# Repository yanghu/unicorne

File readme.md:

# Unicorne - A single-piece 40% ortho keyboard inspired by Corne and more.

This is the keyboard design files for my own use, inspired by
[crkbd](https://github.com/foostan/crkbd),
[Kyria](https://blog.splitkb.com/blog/introducing-the-kyria) and
[Ferris](https://github.com/pierrechevalier83/ferris), as well as
[Reviung41](https://github.com/gtips/reviung) and others.

The name means "uni(single-piece)corne".

## Summary of board features

* USB-C connector
* Audio buzzer
* Rotary encoder x 2 (optional)
* Underglow RGB LEDs x8
* SMT32 MCU (STM32F411)
* OLED display
* Column stagger similar to Kyria.
* Corne-style thumb cluster with extra inner key: I feel Kyria's thumb cluster 
is too much and the outer column is hard to reach for me. 
* Thumb cluster shifted 0.25u to the middle.

## Links

* [PCB repo](unicorne-mx/unicorne).
* [PCB ibom
](https://yanghu.github.io/unicorne/artifacts/ibom/unicorn-ibom.html)
* [Fabrication files and firmware](https://github.com/yanghu/unicorne/releases/tag/v1.0)
* [QMK firmware repo](https://github.com/yanghu/qmk_firmware/tree/unicorne/keyboards/yanghu/unicorne).
* [Build guide](https://github.com/yanghu/unicorne/wiki/Build-guide)

## Why I designed this board

I like the simplicity of Corne, however, the more aggresive column stagger
on Kyria suits my hand better. I also removed the use of pro micro boards, and
followed Ferris 2.0 with an ARM chip directly on the board.

The initial reason I wanted to design this board is to eliminate the ugly
"add-on" board of promicro. Ferris is nice but I needed a 3x6 with full thumb
clusters as well: portability is not an issue for me.

I initially thought about building a split keyboard, however, after used crkbd
for a while, I missed the simplicity of a one-piece board: it's always symmetric
and has smaller footprint.

I do use a Planck, but *ortho* is not really a good idea on traditional keyboard
layout: the hands are so close and it's awkward to keep hands "vertical": the
wrist really is painful, especially after used to more ergonomic splits.

Reviung-like keyboards really gave me the inspiration. The angle ensures arms
and hands are in line, while you can still use the ortho layout.

Other features are nice and in different designs. I like the buzzer on Planck
that tells you when the keyboard is alive. The small OLED really is useful to
display status information for a programmable board. The encoder can be pretty
versatile.

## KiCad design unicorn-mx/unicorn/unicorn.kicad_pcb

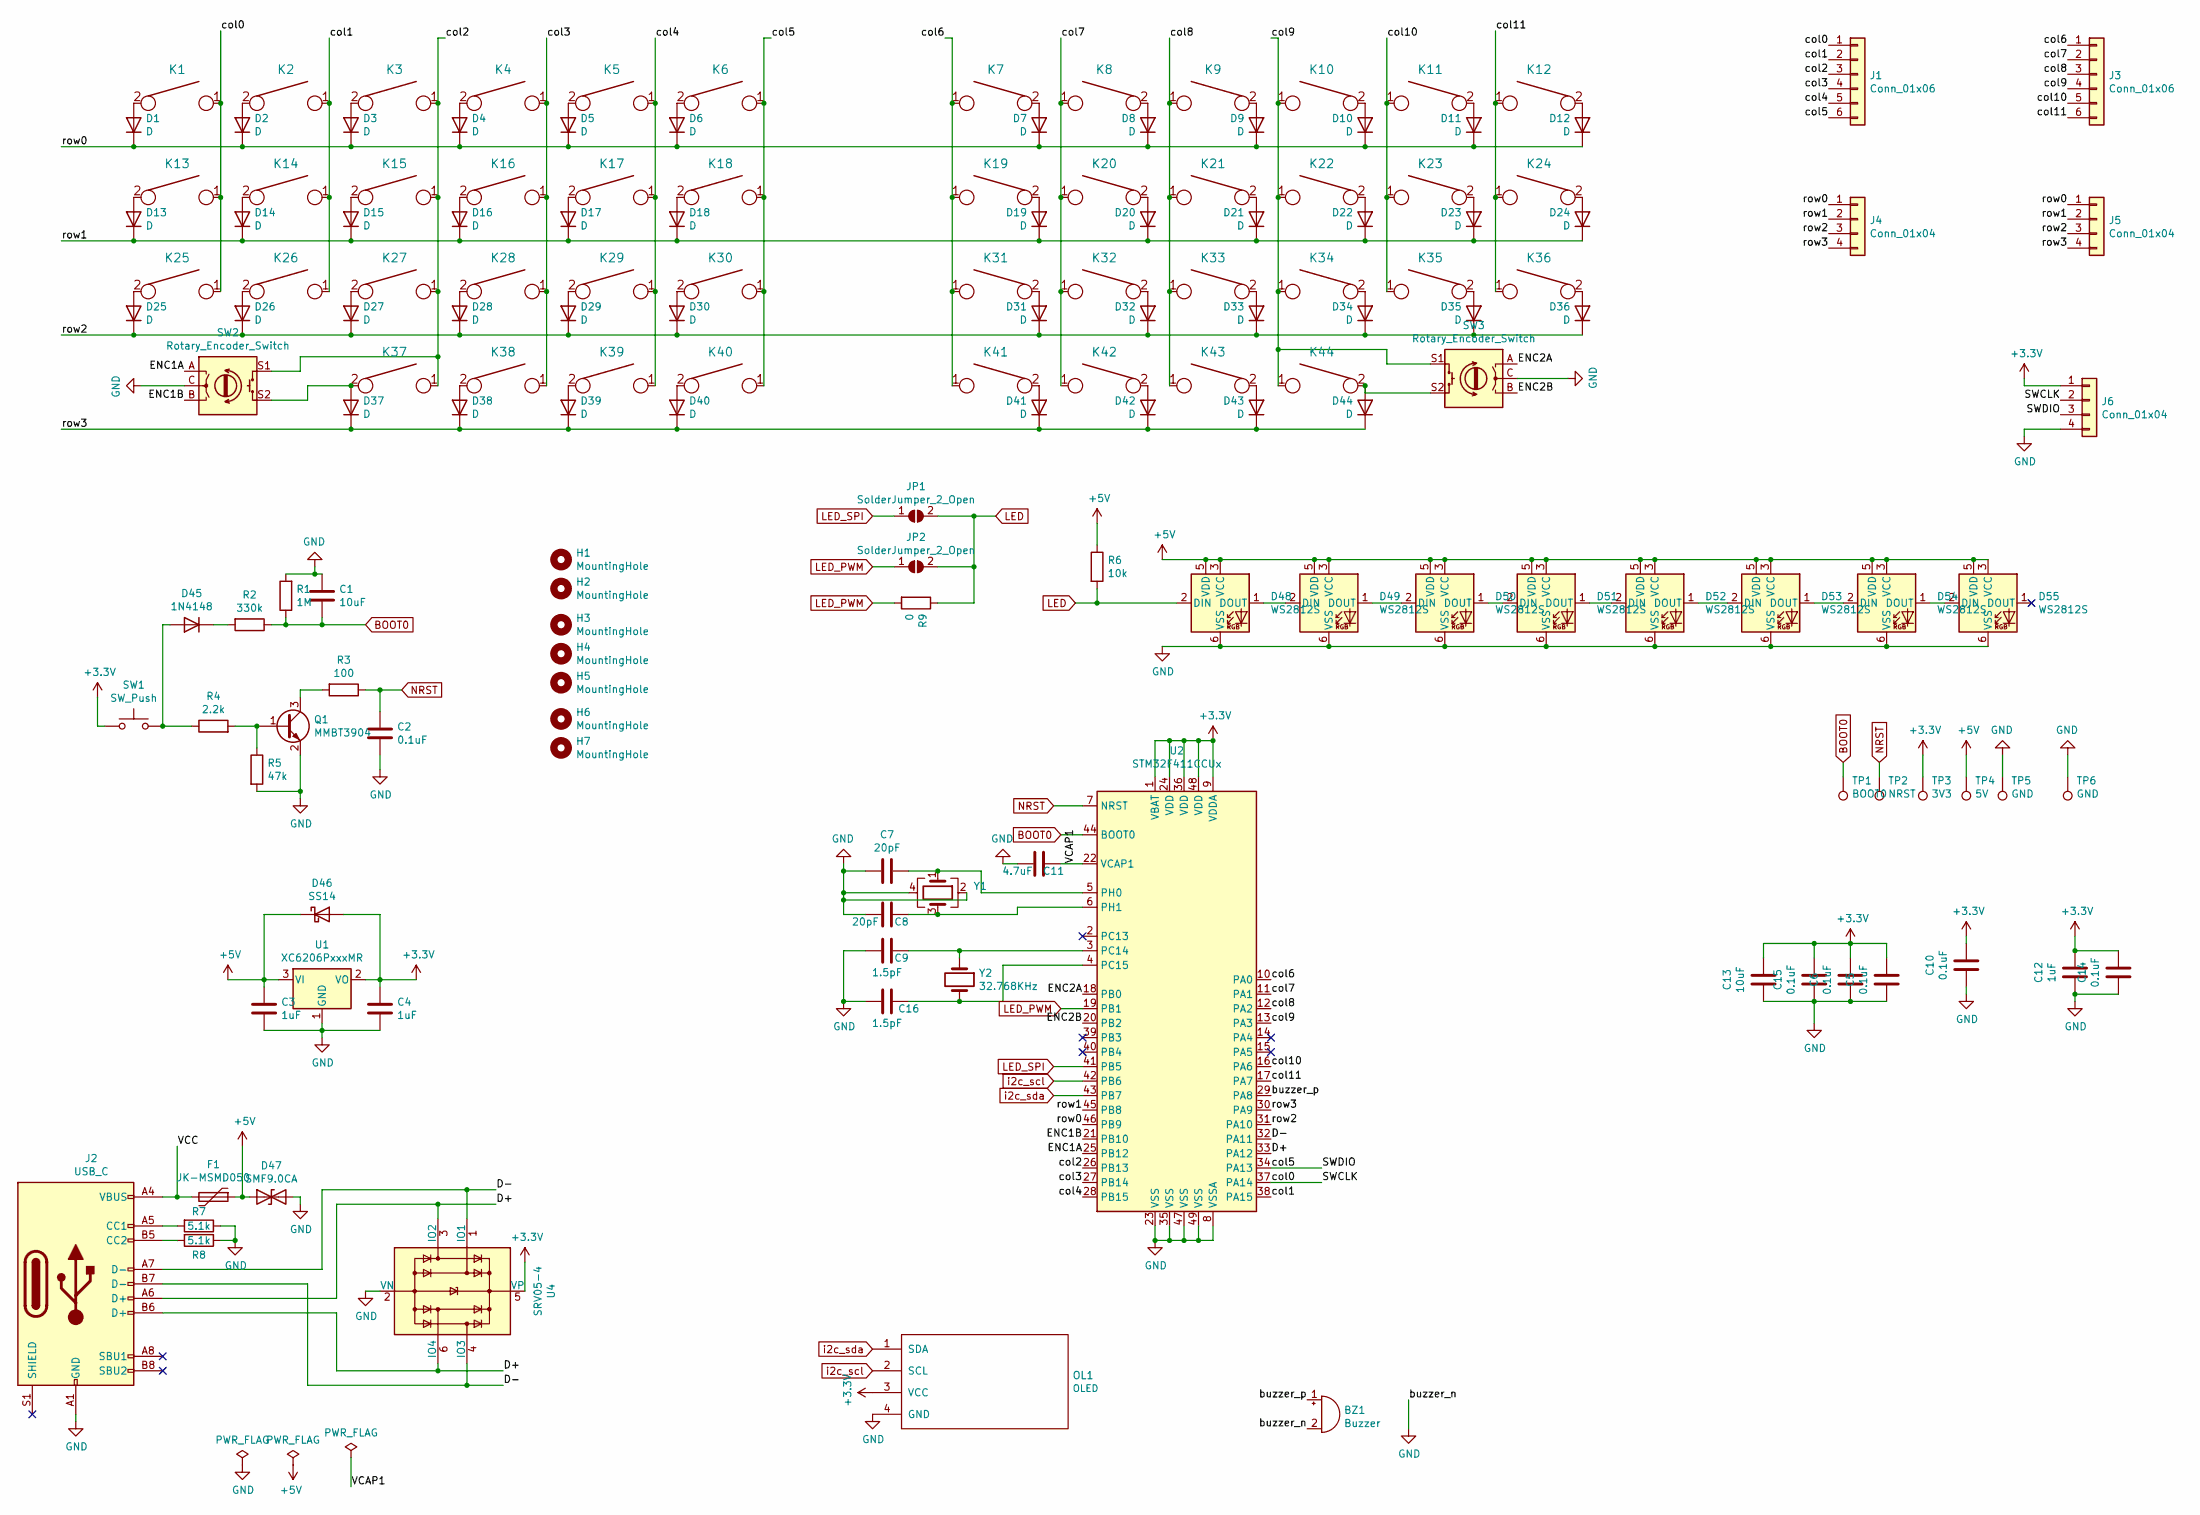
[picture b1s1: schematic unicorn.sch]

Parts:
BZ1: Buzzer; Piezo-KLJ-1625; LCSC Part C201041
C1, C13: 10uF; C_0603_1608Metric; LCSC Part C19702
C2, C5, C6, C10, C14, C15: 0.1uF; C_0603_1608Metric; LCSC Part C14663
C3, C4, C12: 1uF; C_0603_1608Metric; LCSC Part C15849
C7, C8: 20pF; C_0603_1608Metric; LCSC Part C1648
C9, C16: 1.5pF; C_0603_1608Metric; LCSC Part C1639
C11: 4.7uF; C_0603_1608Metric; LCSC Part C19666
D1, D2, D3, D4, D5, D6, D7, D8, D9, D10, D11, D12, D13, D14, D15, D16, D17, D18, D19, D20, D21, D22, D23, D24, D25, D26, D27, D28, D29, D30, D31, D32, D33, D34, D35, D36, D37, D38, D39, D40, D41, D42, D43, D44: D; D_SOD-123; LCSC Part C81598
D45: 1N4148; D_SOD-123; LCSC Part C81598
D46: SS14; D_SMA; LCSC Part C2480
D47: SMF9.0CA; D_SOD-123; LCSC Part C435473
D48, D49, D50, D51, D52, D53, D54, D55: WS2812S; LED_WS2812_PLCC6_5.0x5.0mm_P1.6mm; LCSC Part C114584
F1: JK-MSMD050; Fuse_1812_4532Metric; LCSC Part C369167
H1, H2, H3, H4, H5, H6, H7: MountingHole; MountingHole_4.5mm
J1, J3: Conn_01x06; PinHeader_1x06_P2.54mm_Vertical
J2: USB_C; USB_C_HRO_TYPE-C-31-M-12; LCSC Part C165948
J4, J5, J6: Conn_01x04; PinHeader_1x04_P2.54mm_Vertical
JP1, JP2: SolderJumper_2_Open; SolderJumper-2_P1.3mm_Open_TrianglePad1.0x1.5mm
K1, K2, K3, K4, K5, K6, K7, K8, K9, K10, K11, K12, K13, K14, K15, K16, K17, K18, K19, K20, K21, K22, K23, K24, K25, K26, K27, K28, K29, K30, K31, K32, K33, K34, K35, K36, K37, K38, K39, K42, K43, K44: KEYSW; CherryMX_Hotswap
K40, K41: KEYSW; CherryMX_Hotswap_1.5u
OL1: OLED; OLED_v2
Q1: MMBT3904; SOT-23; LCSC Part C20526
R1: 1M; R_0603_1608Metric; LCSC Part C22935
R2: 330k; R_0603_1608Metric; LCSC Part C23137
R3: 100; R_0603_1608Metric; LCSC Part C22775
R4: 2.2k; R_0603_1608Metric; LCSC Part C4190
R5: 47k; R_0603_1608Metric; LCSC Part C25819
R6: 10k; R_0603_1608Metric; LCSC Part C25804
R7, R8: 5.1k; R_0603_1608Metric; LCSC Part C23186
R9: 0; R_0603_1608Metric; LCSC Part C21189
SW1: SW_Push; SW_SPST_B3U-1000P; LCSC Part C231329
SW2, SW3: Rotary_Encoder_Switch; RotaryEncoder_EC11
TP1: BOOT0; TestPoint_THTPad_D1.5mm_Drill0.7mm
TP2: NRST; TestPoint_THTPad_D1.5mm_Drill0.7mm
TP3: 3V3; TestPoint_THTPad_D1.5mm_Drill0.7mm
TP4: 5V; TestPoint_THTPad_D1.5mm_Drill0.7mm
TP5, TP6: GND; TestPoint_THTPad_D1.5mm_Drill0.7mm
U1: XC6206PxxxMR; SOT-23; LCSC Part C5446
U2: STM32F411CCUx; QFN-48-1EP_7x7mm_P0.5mm_EP5.6x5.6mm; LCSC Part C190642
U4: SRV05-4; SOT-23-6; LCSC Part C85364
Y1: 25M Hz; Crystal_SMD_3225-4Pin_3.2x2.5mm; LCSC Part C9006
Y2: 32.768KHz; Crystal_SMD_3215-2Pin_3.2x1.5mm; LCSC Part C32346

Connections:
+3V3: C4.2, C5.1, C6.1, C10.1, C12.1, C13.1, C14.1, C15.1, D46.2 (A), J6.1, OL1.3 (VCC), SW1.1, TP3.1, U1.2 (VO), U2.1 (VBAT), U2.9 (VDDA), U2.24 (VDD), U2.36 (VDD), U2.48 (VDD), U4.5 (VP)
+5V: C3.2, D46.1 (K), D47.1 (A1), D48.3 (VCC), D48.5 (VDD), D49.3 (VCC), D49.5 (VDD), D50.3 (VCC), D50.5 (VDD), D51.3 (VCC), D51.5 (VDD), D52.3 (VCC), D52.5 (VDD), D53.3 (VCC), D53.5 (VDD), D54.3 (VCC), D54.5 (VDD), D55.3 (VCC), D55.5 (VDD), F1.1, R6.1, TP4.1, U1.3 (VI)
/D+: J2.A6 (D+), J2.B6 (D+), U2.33 (PA12), U4.3 (IO2), U4.6 (IO4)
/D-: J2.A7 (D-), J2.B7 (D-), U2.32 (PA11), U4.1 (IO1), U4.4 (IO3)
/ENC1A: SW2.A, U2.25 (PB12)
/ENC1B: SW2.B, U2.21 (PB10)
/ENC2A: SW3.A, U2.18 (PB0)
/ENC2B: SW3.B, U2.20 (PB2)
/SWCLK: J1.1, J6.2, K1.1, K13.1, K25.1, U2.37 (PA14)
/SWDIO: J1.6, J6.3, K6.1, K18.1, K30.1, K40.1, U2.34 (PA13)
/VCAP1: C11.2, U2.22 (VCAP1)
/VCC: F1.2, J2.A4 (VBUS), J2.A9 (VBUS), J2.B4 (VBUS), J2.B9 (VBUS)
/buzzer_p: BZ1.1 (-), U2.29 (PA8)
/col1: J1.2, K2.1, K14.1, K26.1, U2.38 (PA15)
/col2: J1.3, K3.1, K15.1, K27.1, K37.1, SW2.S1, U2.26 (PB13)
/col3: J1.4, K4.1, K16.1, K28.1, K38.1, U2.27 (PB14)
/col4: J1.5, K5.1, K17.1, K29.1, K39.1, U2.28 (PB15)
/col6: J3.1, K7.1, K19.1, K31.1, K41.1, U2.10 (PA0)
/col7: J3.2, K8.1, K20.1, K32.1, K42.1, U2.11 (PA1)
/col8: J3.3, K9.1, K21.1, K33.1, K43.1, U2.12 (PA2)
/col9: J3.4, K10.1, K22.1, K34.1, K44.1, SW3.S1, U2.13 (PA3)
/col10: J3.5, K11.1, K23.1, K35.1, U2.16 (PA6)
/col11: J3.6, K12.1, K24.1, K36.1, U2.17 (PA7)
/row0: D1.1 (K), D2.1 (K), D3.1 (K), D4.1 (K), D5.1 (K), D6.1 (K), D7.1 (K), D8.1 (K), D9.1 (K), D10.1 (K), D11.1 (K), D12.1 (K), J4.1, J5.1, U2.46 (PB9)
/row1: D13.1 (K), D14.1 (K), D15.1 (K), D16.1 (K), D17.1 (K), D18.1 (K), D19.1 (K), D20.1 (K), D21.1 (K), D22.1 (K), D23.1 (K), D24.1 (K), J4.2, J5.2, U2.45 (PB8)
/row2: D25.1 (K), D26.1 (K), D27.1 (K), D28.1 (K), D29.1 (K), D30.1 (K), D31.1 (K), D32.1 (K), D33.1 (K), D34.1 (K), D35.1 (K), D36.1 (K), J4.3, J5.3, U2.31 (PA10)
/row3: D37.1 (K), D38.1 (K), D39.1 (K), D40.1 (K), D41.1 (K), D42.1 (K), D43.1 (K), D44.1 (K), J4.4, J5.4, U2.30 (PA9)
BOOT0: C1.1, R1.1, R2.1, TP1.1, U2.44 (BOOT0)
GND: BZ1.2 (+), C1.2, C2.1, C3.1, C4.1, C5.2, C6.2, C7.2, C8.2, C9.2, C10.2, C11.1, C12.2, C13.2, C14.2, C15.2, C16.2, D47.2 (A2), D48.6 (VSS), D49.6 (VSS), D50.6 (VSS), D51.6 (VSS), D52.6 (VSS), D53.6 (VSS), D54.6 (VSS), D55.6 (VSS), J2.A1 (GND), J2.A12 (GND), J2.B1 (GND), J2.B12 (GND), J6.4, OL1.4 (GND), Q1.2 (E), R1.2, R5.2, R7.1, R8.1, SW2.C, SW3.C, TP5.1, TP6.1, U1.1 (GND), U2.8 (VSSA), U2.23 (VSS), U2.35 (VSS), U2.47 (VSS), U2.49 (VSS), U4.2 (VN), Y1.2, Y1.4
LED: D48.2 (DIN), JP1.2 (B), JP2.2 (B), R6.2, R9.1
LED_PWM: JP2.1 (A), R9.2, U2.19 (PB1)
LED_SPI: JP1.1 (A), U2.41 (PB5)
NRST: C2.2, R3.1, TP2.1, U2.7 (NRST)
unnamed: C7.1, U2.5 (PH0), Y1.1
unnamed: C8.1, U2.6 (PH1), Y1.3
unnamed: C9.1, U2.3 (PC14), Y2.1
unnamed: C16.1, U2.4 (PC15), Y2.2
unnamed: D1.2 (A), K1.2
unnamed: D2.2 (A), K2.2
unnamed: D3.2 (A), K3.2
unnamed: D4.2 (A), K4.2
unnamed: D5.2 (A), K5.2
unnamed: D6.2 (A), K6.2
unnamed: D7.2 (A), K7.2
unnamed: D8.2 (A), K8.2
unnamed: D9.2 (A), K9.2
unnamed: D10.2 (A), K10.2
unnamed: D11.2 (A), K11.2
unnamed: D12.2 (A), K12.2
unnamed: D13.2 (A), K13.2
unnamed: D14.2 (A), K14.2
unnamed: D15.2 (A), K15.2
unnamed: D16.2 (A), K16.2
unnamed: D17.2 (A), K17.2
unnamed: D18.2 (A), K18.2
unnamed: D19.2 (A), K19.2
unnamed: D20.2 (A), K20.2
unnamed: D21.2 (A), K21.2
unnamed: D22.2 (A), K22.2
unnamed: D23.2 (A), K23.2
unnamed: D24.2 (A), K24.2
unnamed: D25.2 (A), K25.2
unnamed: D26.2 (A), K26.2
unnamed: D27.2 (A), K27.2
unnamed: D28.2 (A), K28.2
unnamed: D29.2 (A), K29.2
unnamed: D30.2 (A), K30.2
unnamed: D31.2 (A), K31.2
unnamed: D32.2 (A), K32.2
unnamed: D33.2 (A), K33.2
unnamed: D34.2 (A), K34.2
unnamed: D35.2 (A), K35.2
unnamed: D36.2 (A), K36.2
unnamed: D37.2 (A), K37.2, SW2.S2
unnamed: D38.2 (A), K38.2
unnamed: D39.2 (A), K39.2
unnamed: D40.2 (A), K40.2
unnamed: D41.2 (A), K41.2
unnamed: D42.2 (A), K42.2
unnamed: D43.2 (A), K43.2
unnamed: D44.2 (A), K44.2, SW3.S2
unnamed: D45.1 (K), R2.2
unnamed: D45.2 (A), R4.1, SW1.2
unnamed: D48.1 (DOUT), D49.2 (DIN)
unnamed: D49.1 (DOUT), D50.2 (DIN)
unnamed: D50.1 (DOUT), D51.2 (DIN)
unnamed: D51.1 (DOUT), D52.2 (DIN)
unnamed: D52.1 (DOUT), D53.2 (DIN)
unnamed: D53.1 (DOUT), D54.2 (DIN)
unnamed: D54.1 (DOUT), D55.2 (DIN)
unnamed: J2.A5 (CC1), R7.2
unnamed: J2.B5 (CC2), R8.2
unnamed: Q1.1 (B), R4.2, R5.1
unnamed: Q1.3 (C), R3.2
i2c_scl: OL1.2 (SCL), U2.42 (PB6)
i2c_sda: OL1.1 (SDA), U2.43 (PB7)

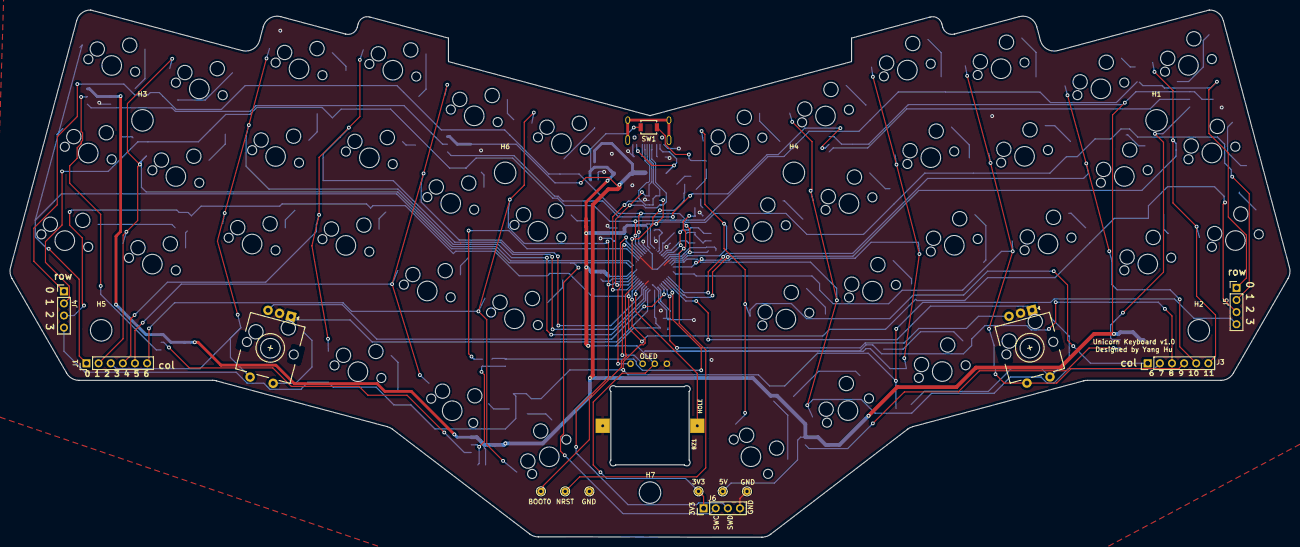
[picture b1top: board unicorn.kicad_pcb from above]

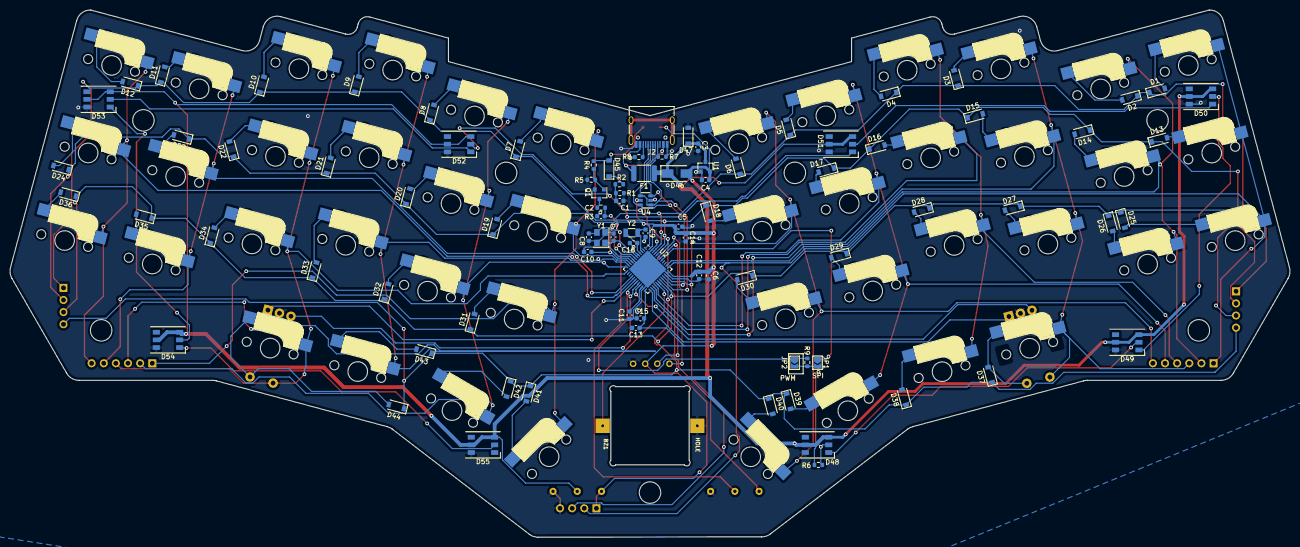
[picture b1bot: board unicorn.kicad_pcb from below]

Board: 2 copper layers, 268.2 x 110.5 mm, 157 parts (90 on the bottom side), 96 nets.

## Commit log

2021-04-09 add keyboard layout dxf and ble board
2021-04-09 add readme
2021-04-09 add symbol and footprint libs
2021-04-09 initial drawing: draw switch array
2021-04-17 layout switches
2021-04-17 add license file
2021-04-18 add outline for choc layout
2021-04-19 routed left half
2021-04-25 add unicorn design
2021-04-25 add 3d models, add oled
2021-04-26 finalize unicorn design
2021-04-30 add plate and bottom, add rendered images
2021-05-07 Add automation files: now use `make unicorn` or `make unicorn-doc` to generate output and `make clean` to clean up
2021-05-07 add bundle files for docs and fab
2021-05-07 update bundle files
2021-05-07 route pcb with new pin assginments, add bridges for led, add test points
2021-05-08 add docs
2021-05-08 use f411 mcu
2021-05-08 fix jlcpcb smt position automation: no need to do extra rotation
2021-05-08 Add back rotation for jlcpcb positions, as most footproints still needs rotation.
2021-05-08 add f072 variant design
2021-05-22 add artifacts folder
2021-05-22 Add build guide.
2021-05-23 remove guide after moved it to wiki
